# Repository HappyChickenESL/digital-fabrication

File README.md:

Run the project with:
npm run dev

generate tailwind output.css:
npx tailwindcss -i ./src/input.css -o ./src/output.css --watch
npx tailwindcss -i ./src/input.css -o ./src/output.css --minify

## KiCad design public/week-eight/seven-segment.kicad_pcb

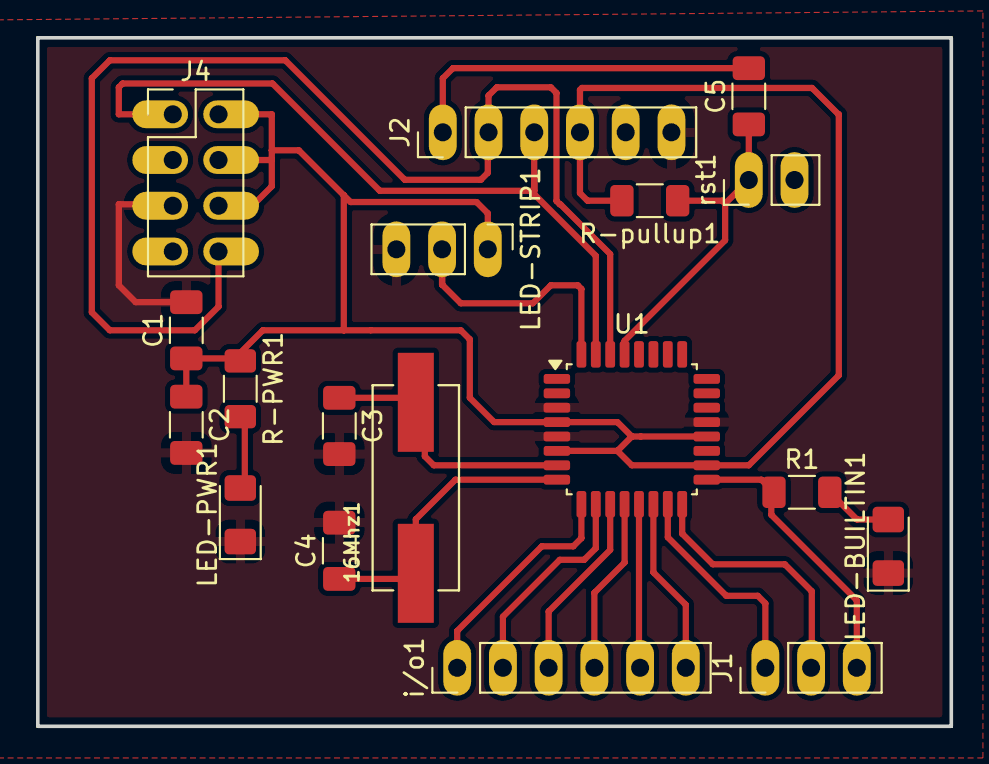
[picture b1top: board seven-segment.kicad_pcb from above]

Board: 2 copper layers, 50.8 x 38.2 mm, 18 parts (0 on the bottom side), 20 nets.

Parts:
16Mhz1: Crystal; crystalSmd
C1: 1 uf; C_1206_3216Metric_Pad1.33x1.80mm_HandSolder
C2: 10 uf; C_1206_3216Metric_Pad1.33x1.80mm_HandSolder
C3, C4: 22 pf; C_1206_3216Metric_Pad1.33x1.80mm_HandSolder
C5: 100 nf; C_1206_3216Metric_Pad1.33x1.80mm_HandSolder
J1: Conn_01x03_Pin; PinHeader_1x03_P2.54mm_Vertical
J2: Conn_01x06_Pin; PinHeader_1x06_P2.54mm_VerticalAA
J4: Conn_WiFi; PinHeader_2x04_P2.54mm_Vertical
LED-BUILTIN1: yellow; LED_1206_3216Metric_Pad1.42x1.75mm_HandSolder
LED-PWR1: Green; LED_1206_3216Metric_Pad1.42x1.75mm_HandSolder
LED-STRIP1: Conn_01x03_Pin; PinHeader_1x03_P2.54mm_Vertical
R1: 499; R_1206_3216Metric_Pad1.30x1.75mm_HandSolder
R-PWR1: 499; R_1206_3216Metric_Pad1.30x1.75mm_HandSolder
R-pullup1: 10k; R_1206_3216Metric_Pad1.30x1.75mm_HandSolder
U1: ATmega328P-A; TQFP-32_7x7mm_P0.8mm
i/o1: Conn_01x06_Pin; PinHeader_1x06_P2.54mm_VerticalAA
rst1: Conn_01x02_Pin; PinHeader_1x02_P2.54mm_Vertical

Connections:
2: LED-STRIP1.2, U1.32 (PD2)
5: U1.9 (PD5), i/o1.1
6: U1.10 (PD6), i/o1.2
7: U1.11 (PD7), i/o1.3
8: U1.12 (PB0), i/o1.4
9: U1.13 (PB1), i/o1.5
10: U1.14 (PB2), i/o1.6
GND: C1.2, C2.2, C3.2, C4.2, J2.6, J4.5, LED-BUILTIN1.1 (K), LED-PWR1.1 (K), LED-STRIP1.3, U1.3 (GND), U1.5 (GND), U1.21 (GND)
unnamed: LED-BUILTIN1.2 (A), R1.2
unnamed: LED-PWR1.2 (A), R-PWR1.2
RXD: J2.2, J4.8, U1.30 (PD0)
TXD: J2.3, J4.1, U1.31 (PD1)
VCC: C1.1, C2.1, J2.4, J4.2, J4.4, J4.6, LED-STRIP1.1, R-PWR1.1, R-pullup1.2, U1.4 (VCC), U1.6 (VCC), U1.18 (AVCC), U1.20 (AREF)
miso: J1.2, U1.16 (PB4)
mosi: J1.1, U1.15 (PB3)
rst: C5.1, R-pullup1.1, U1.29 (~RESET/PC6), rst1.1
rstFTDI: C5.2, J2.1
sck: J1.3, R1.1, U1.17 (PB5)
xtal1: 16Mhz1.2, C3.1, U1.7 (XTAL1/PB6)
xtal2: 16Mhz1.1, C4.1, U1.8 (XTAL2/PB7)

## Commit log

2025-10-13 init
2025-10-13 init2
2025-10-13 Create CNAME
2025-10-13 basic design
2025-10-13 setup action
    Change artifact upload path to only include the 'src' directory.
2025-10-13 basic week 1
2025-10-13 added about text
2025-10-17 swapped to react
2025-10-17 added basic layout
2025-10-17 added content
2025-10-20 added assignment week two
2025-10-20 fixed layout
2025-10-20 fixed images
2025-10-20 potential image fix
2025-10-20 fixed routing issue
2025-10-27 added assignment 3
2025-10-27 working late
2025-11-03 finished assignment four
2025-11-10 added assignment five
2025-11-17 added assignment six
2025-11-24 added assignment seven
2026-02-16 created final documentation
2026-02-16 added poster
